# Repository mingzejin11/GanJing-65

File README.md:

# GanJing 65
**A 65% keyboard with a rotary encoder, OLED screen and USB-c. Made using only through-hole components for easy soldering.**

[Bill of materials](https://octopart.com/bom-tool/HPiXAxIx)

## Layout options
The GanJing keyboard supports ISO layouts, as well as stepped caps lock keys. The bottom row also supports alternate layouts.

## Schematic
Inspired by the [Discipline](https://github.com/coseyfannitutti/discipline) and [Pheromone](https://github.com/luantty2/pheromone_keyboard) keyboards.

## PCB layout
### Front

### Back

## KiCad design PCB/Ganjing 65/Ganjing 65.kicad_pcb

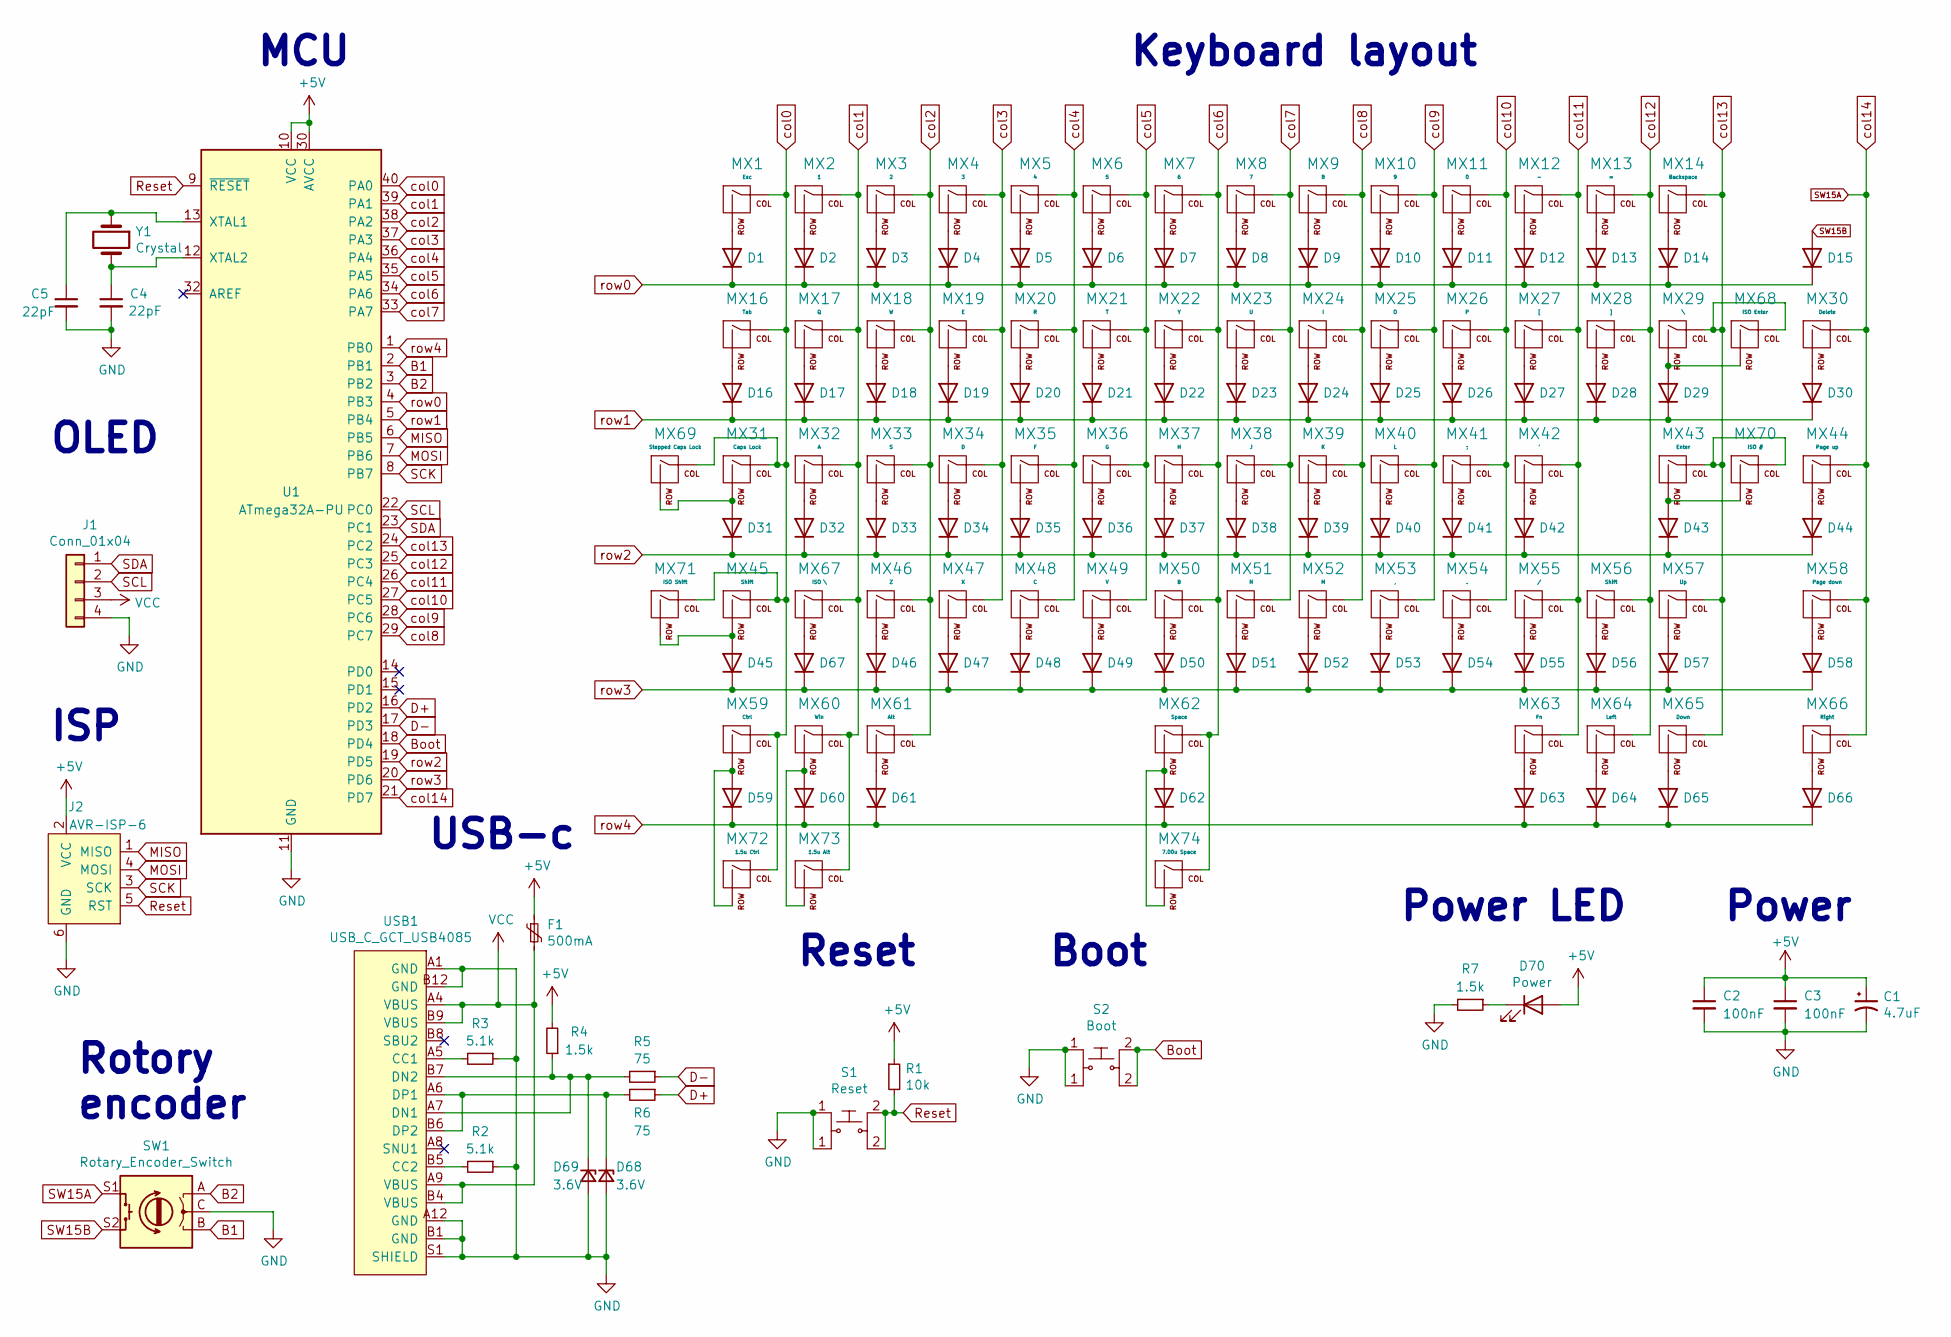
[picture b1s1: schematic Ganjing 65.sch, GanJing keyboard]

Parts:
C1: 4.7uF; CP_Radial_D4.0mm_P1.50mm; Mouser # 647-UMT1H4R7MDD1TP
C2, C3: 100nF; C_Disc_D4.3mm_W1.9mm_P5.00mm
C4, C5: 22pF; C_Disc_D3.0mm_W1.6mm_P2.50mm; Digikey # 490-11879-ND
D1, D2, D3, D4, D5, D6, D7, D8, D9, D10, D11, D12, D13, D14, D15, D16, D17, D18, D19, D20, D21, D22, D23, D24, D25, D26, D27, D28, D29, D30, D31, D32, D33, D34, D35, D36, D37, D38, D39, D40, D41, D42, D43, D44, D45, D46, D47, D48, D49, D50, D51, D52, D53, D54, D55, D56, D57, D58, D59, D60, D61, D62, D63, D64, D65, D66, D67: D; D_DO-35_SOD27_P5.08mm_Horizontal; Digikey # 1N4148FSTR-ND
D68, D69: 3.6V; D_DO-35_SOD27_P5.08mm_Horizontal; Mouser # 78-TZX3V6A
D70: Power; LED_D3.0mm; Digikey # 160-1140-ND
F1: 500mA; polyfuse_5.1mm; Digikey # MF-R050-ND
J1: Conn_01x04; ssd1306_128x32_oled
J2: AVR-ISP-6; AVR_ICSP_3x2; Digikey # 609-4934-ND
MX1: Esc; MXOnly-1U-NoLED
MX2: 1; MXOnly-1U-NoLED
MX3: 2; MXOnly-1U-NoLED
MX4: 3; MXOnly-1U-NoLED
MX5: 4; MXOnly-1U-NoLED
MX6: 5; MXOnly-1U-NoLED
MX7: 6; MXOnly-1U-NoLED
MX8: 7; MXOnly-1U-NoLED
MX9: 8; MXOnly-1U-NoLED
MX10: 9; MXOnly-1U-NoLED
MX11: 0; MXOnly-1U-NoLED
MX12: -; MXOnly-1U-NoLED
MX13: =; MXOnly-1U-NoLED
MX14: Backspace; MXOnly-2U-NoLED
MX16: Tab; MXOnly-1.5U-NoLED
MX17: Q; MXOnly-1U-NoLED
MX18: W; MXOnly-1U-NoLED
MX19: E; MXOnly-1U-NoLED
MX20: R; MXOnly-1U-NoLED
MX21: T; MXOnly-1U-NoLED
MX22: Y; MXOnly-1U-NoLED
MX23: U; MXOnly-1U-NoLED
MX24: I; MXOnly-1U-NoLED
MX25: O; MXOnly-1U-NoLED
MX26: P; MXOnly-1U-NoLED
MX27: [; MXOnly-1U-NoLED
MX28: ]; MXOnly-1U-NoLED
MX29: \\; MXOnly-1.5U-NoLED
MX30: Delete; MXOnly-1U-NoLED
MX31: Caps Lock; MXOnly-1.75U-NoLED
MX32: A; MXOnly-1U-NoLED
MX33: S; MXOnly-1U-NoLED
MX34: D; MXOnly-1U-NoLED
MX35: F; MXOnly-1U-NoLED
MX36: G; MXOnly-1U-NoLED
MX37: H; MXOnly-1U-NoLED
MX38: J; MXOnly-1U-NoLED
MX39: K; MXOnly-1U-NoLED
MX40: L; MXOnly-1U-NoLED
MX41: ;; MXOnly-1U-NoLED
MX42: '; MXOnly-1U-NoLED
MX43: Enter; MXOnly-2.25U-NoLED
MX44: Page up; MXOnly-1U-NoLED
MX45: Shift; MXOnly-2.25U-NoLED
MX46: Z; MXOnly-1U-NoLED
MX47: X; MXOnly-1U-NoLED
MX48: C; MXOnly-1U-NoLED
MX49: V; MXOnly-1U-NoLED
MX50: B; MXOnly-1U-NoLED
MX51: N; MXOnly-1U-NoLED
MX52: M; MXOnly-1U-NoLED
MX53: ,; MXOnly-1U-NoLED
MX54: .; MXOnly-1U-NoLED
MX55: /; MXOnly-1U-NoLED
MX56: Shift; MXOnly-1.75U-NoLED
MX57: Up; MXOnly-1U-NoLED
MX58: Page down; MXOnly-1U-NoLED
MX59: Ctrl; MXOnly-1.25U-NoLED
MX60: Win; MXOnly-1.25U-NoLED
MX61: Alt; MXOnly-1.25U-NoLED
MX62: Space; MXOnly-6.25U-ReversedStabilizers-NoLED
MX63: Fn; MXOnly-1U-NoLED
MX64: Left; MXOnly-1U-NoLED
MX65: Down; MXOnly-1U-NoLED
MX66: Right; MXOnly-1U-NoLED
MX67: ISO \\; MXOnly-1U-NoLED
MX68: ISO Enter; MXOnly-ISO-ReversedStabilizers-NoLED
MX69: Stepped Caps Lock; MXOnly-1.75U-Stepped-NoLED
MX70: ISO #; MXOnly-1U-NoLED
MX71: ISO Shift; MXOnly-1.25U-NoLED
MX72: 1.5u Ctrl; MXOnly-1.5U-NoLED
MX73: 1.5u Alt; MXOnly-1.5U-NoLED
MX74: 7.00u Space; MXOnly-7U-ReversedStabilizers-NoLED
R1: 10k; R_Axial_DIN0204_L3.6mm_D1.6mm_P5.08mm_Horizontal
R2, R3: 5.1k; R_Axial_DIN0204_L3.6mm_D1.6mm_P5.08mm_Horizontal; Mouser # 603-MFR-12FTF52-5K1
R4, R7: 1.5k; R_Axial_DIN0204_L3.6mm_D1.6mm_P5.08mm_Horizontal; Mouser # 603-MFR-12FTF52-1K5
R5, R6: 75; R_Axial_DIN0204_L3.6mm_D1.6mm_P5.08mm_Horizontal; Mouser # 603-CFR-12JR-52-75R
S1: Reset; SW_PUSH_6mm
S2: Boot; SW_PUSH_6mm
SW1: Rotary_Encoder_Switch; RotaryEncoder_Alps_EC11E-Switch_Vertical_H20mm; Mouser # 688-EC11E183440C
U1: ATmega32A-PU; DIP-40_W15.24mm; Digikey # ATMEGA32A-PU-ND
USB1: USB_C_GCT_USB4085; Digikey # 2073-USB4085-GF-ATR-ND
Y1: Crystal; Crystal_HC49-4H_Vertical; Mouser # 815-ABL16000MHZB4YT

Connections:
+5V: C1.1, C2.1, C3.1, D70.2 (A), F1.1, J2.2 (VCC), R1.1, R4.2, U1.10 (VCC), U1.30 (AVCC)
B1: SW1.B, U1.2 (PB1)
B2: SW1.A, U1.3 (PB2)
Boot: S2.2, U1.18 (PD4)
D+: R6.1, U1.16 (PD2)
D-: R5.1, U1.17 (PD3)
GND: C1.2, C2.2, C3.2, C4.2, C5.2, D68.2 (A), D69.2 (A), J1.4, J2.6 (GND), R2.1, R3.1, R7.2, S1.1, S2.1, SW1.C, U1.11 (GND), U1.31 (GND), USB1.A1 (GND), USB1.A12 (GND), USB1.B1 (GND), USB1.B12 (GND), USB1.S1 (SHIELD)
MISO: J2.1 (MISO), U1.6 (PB5)
MOSI: J2.4 (MOSI), U1.7 (PB6)
unnamed: C4.1, U1.12 (XTAL2), Y1.2
unnamed: C5.1, U1.13 (XTAL1), Y1.1
unnamed: D1.2, MX1.2 (ROW)
unnamed: D2.2, MX2.2 (ROW)
unnamed: D3.2, MX3.2 (ROW)
unnamed: D4.2, MX4.2 (ROW)
unnamed: D5.2, MX5.2 (ROW)
unnamed: D6.2, MX6.2 (ROW)
unnamed: D7.2, MX7.2 (ROW)
unnamed: D8.2, MX8.2 (ROW)
unnamed: D9.2, MX9.2 (ROW)
unnamed: D10.2, MX10.2 (ROW)
unnamed: D11.2, MX11.2 (ROW)
unnamed: D12.2, MX12.2 (ROW)
unnamed: D13.2, MX13.2 (ROW)
unnamed: D14.2, MX14.2 (ROW)
unnamed: D16.2, MX16.2 (ROW)
unnamed: D17.2, MX17.2 (ROW)
unnamed: D18.2, MX18.2 (ROW)
unnamed: D19.2, MX19.2 (ROW)
unnamed: D20.2, MX20.2 (ROW)
unnamed: D21.2, MX21.2 (ROW)
unnamed: D22.2, MX22.2 (ROW)
unnamed: D23.2, MX23.2 (ROW)
unnamed: D24.2, MX24.2 (ROW)
unnamed: D25.2, MX25.2 (ROW)
unnamed: D26.2, MX26.2 (ROW)
unnamed: D27.2, MX27.2 (ROW)
unnamed: D28.2, MX28.2 (ROW)
unnamed: D29.2, MX29.2 (ROW), MX68.2 (ROW)
unnamed: D30.2, MX30.2 (ROW)
unnamed: D31.2, MX31.2 (ROW), MX69.2 (ROW)
unnamed: D32.2, MX32.2 (ROW)
unnamed: D33.2, MX33.2 (ROW)
unnamed: D34.2, MX34.2 (ROW)
unnamed: D35.2, MX35.2 (ROW)
unnamed: D36.2, MX36.2 (ROW)
unnamed: D37.2, MX37.2 (ROW)
unnamed: D38.2, MX38.2 (ROW)
unnamed: D39.2, MX39.2 (ROW)
unnamed: D40.2, MX40.2 (ROW)
unnamed: D41.2, MX41.2 (ROW)
unnamed: D42.2, MX42.2 (ROW)
unnamed: D43.2, MX43.2 (ROW), MX70.2 (ROW)
unnamed: D44.2, MX44.2 (ROW)
unnamed: D45.2, MX45.2 (ROW), MX71.2 (ROW)
unnamed: D46.2, MX46.2 (ROW)
unnamed: D47.2, MX47.2 (ROW)
unnamed: D48.2, MX48.2 (ROW)
unnamed: D49.2, MX49.2 (ROW)
unnamed: D50.2, MX50.2 (ROW)
unnamed: D51.2, MX51.2 (ROW)
unnamed: D52.2, MX52.2 (ROW)
unnamed: D53.2, MX53.2 (ROW)
unnamed: D54.2, MX54.2 (ROW)
unnamed: D55.2, MX55.2 (ROW)
unnamed: D56.2, MX56.2 (ROW)
unnamed: D57.2, MX57.2 (ROW)
unnamed: D58.2, MX58.2 (ROW)
unnamed: D59.2, MX59.2 (ROW), MX72.2 (ROW)
unnamed: D60.2, MX60.2 (ROW), MX73.2 (ROW)
unnamed: D61.2, MX61.2 (ROW)
unnamed: D62.2, MX62.2 (ROW), MX74.2 (ROW)
unnamed: D63.2, MX63.2 (ROW)
unnamed: D64.2, MX64.2 (ROW)
unnamed: D65.2, MX65.2 (ROW)
unnamed: D66.2, MX66.2 (ROW)
unnamed: D67.2, MX67.2 (ROW)
unnamed: D68.1 (K), R6.2, USB1.A6 (DP1), USB1.B6 (DP2)
unnamed: D69.1 (K), R4.1, R5.2, USB1.A7 (DN1), USB1.B7 (DN2)
unnamed: D70.1 (K), R7.1
unnamed: R2.2, USB1.B5 (CC2)
unnamed: R3.2, USB1.A5 (CC1)
Reset: J2.5 (RST), R1.2, S1.2, U1.9 (~RESET)
SCK: J2.3 (SCK), U1.8 (PB7)
SCL: J1.2, U1.22 (PC0)
SDA: J1.1, U1.23 (PC1)
SW15A: MX30.1 (COL), MX44.1 (COL), MX58.1 (COL), MX66.1 (COL), SW1.S1, U1.21 (PD7)
SW15B: D15.2, SW1.S2
VCC: F1.2, J1.3, USB1.A4 (VBUS), USB1.A9 (VBUS), USB1.B4 (VBUS), USB1.B9 (VBUS)
col0: MX1.1 (COL), MX16.1 (COL), MX31.1 (COL), MX45.1 (COL), MX59.1 (COL), MX69.1 (COL), MX71.1 (COL), MX72.1 (COL), U1.40 (PA0)
col1: MX2.1 (COL), MX17.1 (COL), MX32.1 (COL), MX60.1 (COL), MX67.1 (COL), MX73.1 (COL), U1.39 (PA1)
col2: MX3.1 (COL), MX18.1 (COL), MX33.1 (COL), MX46.1 (COL), MX61.1 (COL), U1.38 (PA2)
col3: MX4.1 (COL), MX19.1 (COL), MX34.1 (COL), MX47.1 (COL), U1.37 (PA3)
col4: MX5.1 (COL), MX20.1 (COL), MX35.1 (COL), MX48.1 (COL), U1.36 (PA4)
col5: MX6.1 (COL), MX21.1 (COL), MX36.1 (COL), MX49.1 (COL), U1.35 (PA5)
col6: MX7.1 (COL), MX22.1 (COL), MX37.1 (COL), MX50.1 (COL), MX62.1 (COL), MX74.1 (COL), U1.34 (PA6)
col7: MX8.1 (COL), MX23.1 (COL), MX38.1 (COL), MX51.1 (COL), U1.33 (PA7)
col8: MX9.1 (COL), MX24.1 (COL), MX39.1 (COL), MX52.1 (COL), U1.29 (PC7)
col9: MX10.1 (COL), MX25.1 (COL), MX40.1 (COL), MX53.1 (COL), U1.28 (PC6)
col10: MX11.1 (COL), MX26.1 (COL), MX41.1 (COL), MX54.1 (COL), U1.27 (PC5)
col11: MX12.1 (COL), MX27.1 (COL), MX42.1 (COL), MX55.1 (COL), MX63.1 (COL), U1.26 (PC4)
col12: MX13.1 (COL), MX28.1 (COL), MX56.1 (COL), MX64.1 (COL), U1.25 (PC3)
col13: MX14.1 (COL), MX29.1 (COL), MX43.1 (COL), MX57.1 (COL), MX65.1 (COL), MX68.1 (COL), MX70.1 (COL), U1.24 (PC2)
row0: D1.1, D2.1, D3.1, D4.1, D5.1, D6.1, D7.1, D8.1, D9.1, D10.1, D11.1, D12.1, D13.1, D14.1, D15.1, U1.4 (PB3)
row1: D16.1, D17.1, D18.1, D19.1, D20.1, D21.1, D22.1, D23.1, D24.1, D25.1, D26.1, D27.1, D28.1, D29.1, D30.1, U1.5 (PB4)
row2: D31.1, D32.1, D33.1, D34.1, D35.1, D36.1, D37.1, D38.1, D39.1, D40.1, D41.1, D42.1, D43.1, D44.1, U1.19 (PD5)
row3: D45.1, D46.1, D47.1, D48.1, D49.1, D50.1, D51.1, D52.1, D53.1, D54.1, D55.1, D56.1, D57.1, D58.1, D67.1, U1.20 (PD6)
row4: D59.1, D60.1, D61.1, D62.1, D63.1, D64.1, D65.1, D66.1, U1.1 (PB0)

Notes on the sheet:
Rotory encoder
Keyboard layout
OLED
ISP
MCU
Power
Reset
Power LED
USB-c
Boot

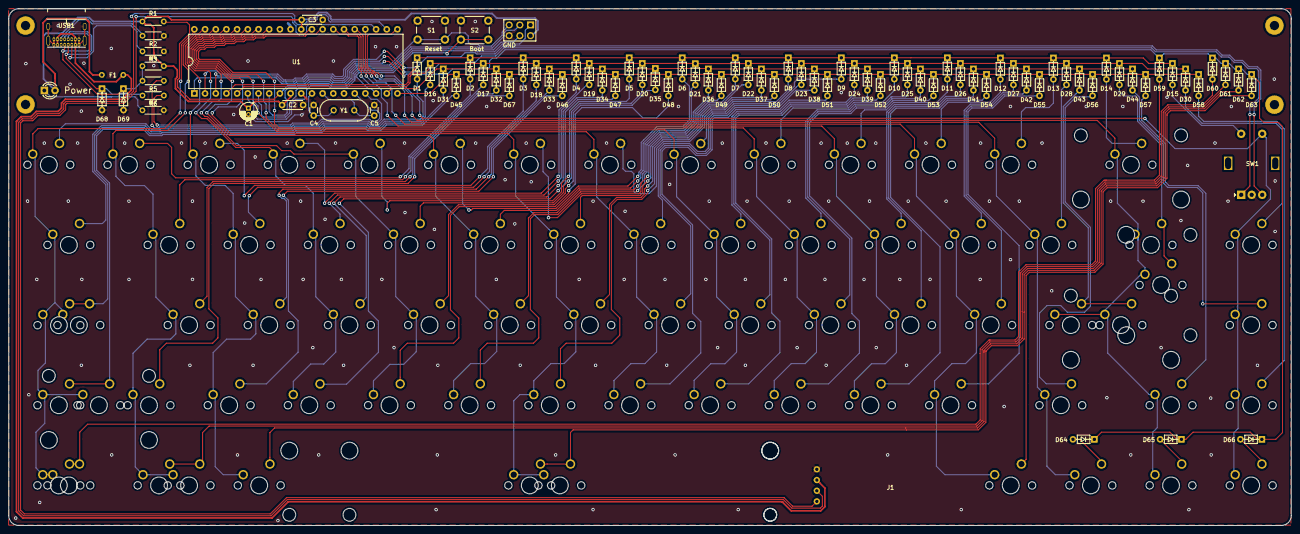
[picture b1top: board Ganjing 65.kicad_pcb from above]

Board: 2 copper layers, 304.8 x 122.8 mm, 169 parts (0 on the bottom side), 108 nets.

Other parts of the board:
L1: LOGO; GanJing logo
REF1, REF2, REF6: MountingHole_2.2mm_M2_Pad
REFl: MountingHole_2.2mm_M2_Pad

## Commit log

2020-08-30 inital commit
2020-09-01 Finished schematic
2020-09-01 adding PDF of schematic
2020-09-01 Updated schematic with reference values
2020-09-01 Added part numbers, links, and datasheets to all symbols, as well as changing the 60 ohm resistor to 62 ohm. All symbols now have associated footprints
2020-09-01 Organizing some files
2020-09-01 Changing README
2020-09-01 changed a jpg to a png
2020-09-01 adding new images
2020-09-01 More housekeeping
2020-09-01 Rearranging pins on MCU
2020-09-01 Ratnest
2020-09-02 Beginning work on PCB layout
2020-09-03 Saving progress on PCB layout
2020-09-03 Wired together all switch columns
2020-09-03 Optimizing some routes
2020-09-04 Finished USB-c routing
2020-09-04 More routing progress
2020-09-04 More routing
2020-09-08 Almost done routing
2020-09-09 routed the encoder and rearranged the diodes
2020-09-09 finished routing
2020-09-09 New images
2020-09-09 Editting some photos
2020-09-09 adding gerber files
2020-09-09 Zipped gerber files
2020-09-10 Cleaning up routing
2020-09-10 More cleaning up
2020-09-10 Even more cleaning on the bottom copper layer
2020-09-10 Cleaning up top copper layer
2020-09-10 Finished cleaning up top copper pour
2020-09-10 Almost done routing clean up
2020-09-11 Updating packages and reducing empty copper pours
2020-09-11 Fixing one picture
2020-09-11 Removing one image
2020-09-11 Adding a photo
2020-09-11 Updating Gerber filesS
2020-09-11 Added remaining mounting holes
2020-09-13 Done adding via stitching
2020-09-13 Generated Gerber files
2020-09-14 Changing footprint for crystal and adding some silk screen text
2020-09-22 Getting started on firmware and case design
2020-09-22 Completed keymaps for ANSI and ISO with winkeyless options
2020-09-22 Added encoder functionality
2020-09-23 Added WPM calculation
2020-09-23 Beginning work on Bongo cat animation
2020-09-25 Working on animation
2020-09-25 Added animation frames
2020-09-25 Adding surrender frames
2020-09-25 Fixing some silk screen stuff on the PCB
2020-09-25 Updating Gerbers
2020-09-25 Minor mistake in text
2020-09-25 Enhancing readability of PCB
2020-09-25 Fixing some formatting
2020-09-29 Adding credits to Pixelbenny for the Bongo cat animation
2020-09-30 Orienting USB-c cutout
2020-09-30 Adding animations
2020-09-30 Upadating vias to be prettier
2020-09-30 Doing some coding woot woot
2020-09-30 Cleaning up the code
2020-10-01 Fixed firmware issues
2020-10-01 Formatting code
2020-10-01 Reducing firmware size
2020-10-01 Minor fixes
2020-10-01 Zip stuff
2020-10-02 removing mp4 file
2020-10-27 Fixing PCB error
2020-10-28 Updating images
2020-11-21 Removing caps lock LED
2020-11-21 Updating images and generating new gerbers
2020-11-24 Adding a dope logo
2020-11-24 Removing unnecessary drill holes
2020-11-24 Cleaning up some routing
2020-11-26 Altering case to centre screw holes and adjust angle of stand to exactly 6 degrees
2020-11-26 Adding OLED cover and adjusting USB-c cut out
2020-11-26 Fixing scaling
2020-12-01 Optimizing case for price
2020-12-01 Adding some new drawings to optomize for laser cutting
2020-12-02 Removing unnecessary files
2020-12-09 Adding 3d models
2020-12-09 Fixing crystal footprint
2020-12-09 Cleaning up silk screen
2020-12-12 cleanimg up file tree
2020-12-12 switching diode names
2020-12-12 Reordering references
2020-12-13 Renaming files
2020-12-13 Changing folder name
2020-12-20 Changing some footprints
2020-12-24 Adding gold lettering
